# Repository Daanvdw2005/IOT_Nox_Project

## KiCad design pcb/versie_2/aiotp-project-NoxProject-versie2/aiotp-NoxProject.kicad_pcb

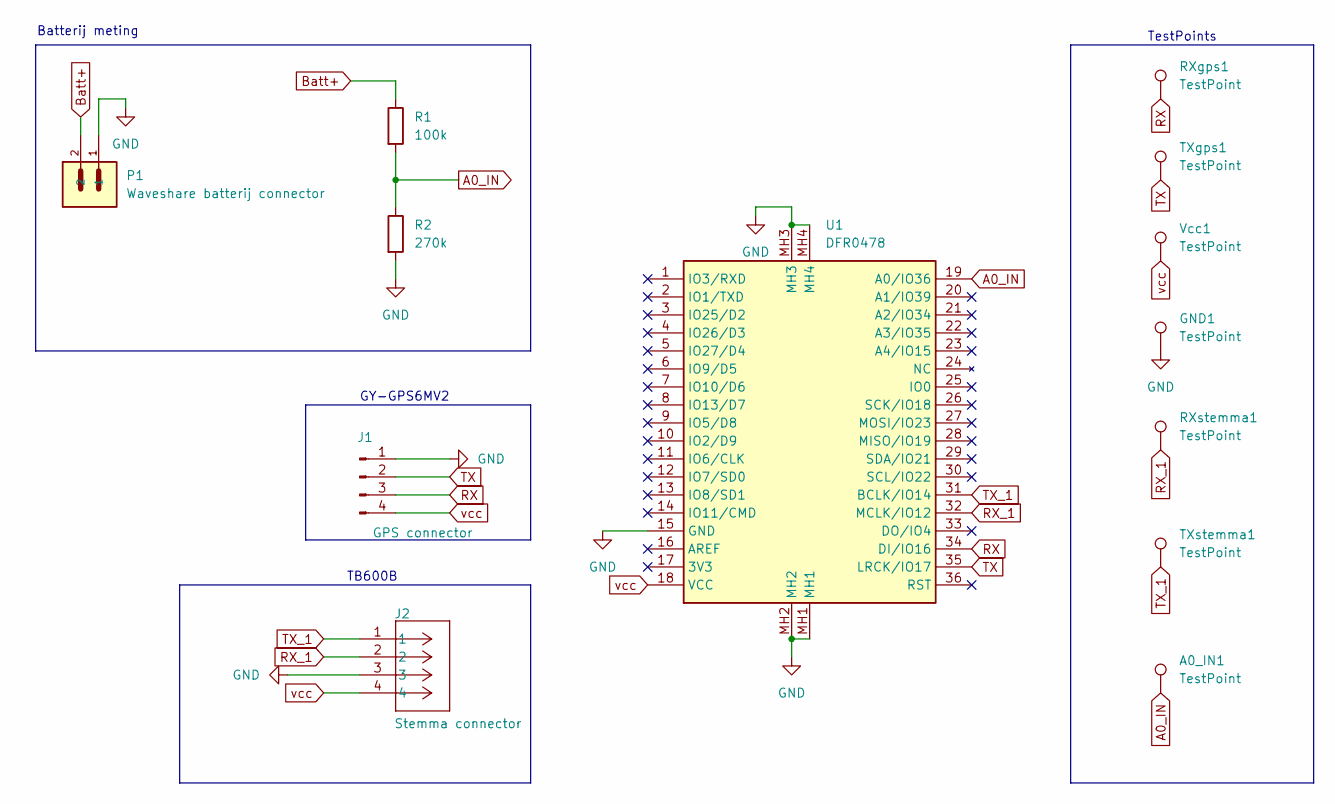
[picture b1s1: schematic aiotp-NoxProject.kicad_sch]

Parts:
A0_IN1: TestPoint; TestPoint_THTPad_D1.0mm_Drill0.5mm
GND1: TestPoint; TestPoint_THTPad_D1.0mm_Drill0.5mm
J1: GPS connector; GY-GPS6MV2
J2: Stemma connector; B4B-ZR; PARTREV N/A
P1: Waveshare batterij connector; JST_S2B-PH-SM4-TB
R1: 100k; R_0805_2012Metric
R2: 270k; R_0805_2012Metric
RXgps1: TestPoint; TestPoint_THTPad_D1.0mm_Drill0.5mm
RXstemma1: TestPoint; TestPoint_THTPad_D1.0mm_Drill0.5mm
TXgps1: TestPoint; TestPoint_THTPad_D1.0mm_Drill0.5mm
TXstemma1: TestPoint; TestPoint_THTPad_D1.0mm_Drill0.5mm
U1: DFR0478; FIREBEETLE_ESP32; Manufacturer_Part_Number DFR0478; Mouser Part Number 426-DFR0478
Vcc1: TestPoint; TestPoint_THTPad_D1.0mm_Drill0.5mm

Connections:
A0_IN: A0_IN1.1, R1.2, R2.1, U1.19 (A0/IO36)
Batt+: P1.2, R1.1
GND: GND1.1, J1.1, J2.3, P1.1, R2.2, U1.15 (GND), U1.MH1, U1.MH2, U1.MH3, U1.MH4
RX: J1.3, RXgps1.1, U1.34 (DI/IO16)
RX_1: J2.2, RXstemma1.1, U1.32 (MCLK/IO12)
TX: J1.2, TXgps1.1, U1.35 (LRCK/IO17)
TX_1: J2.1, TXstemma1.1, U1.31 (BCLK/IO14)
vcc: J1.4, J2.4, U1.18 (VCC), Vcc1.1

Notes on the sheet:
GY-GPS6MV2
TestPoints
Batterij meting
TB600B

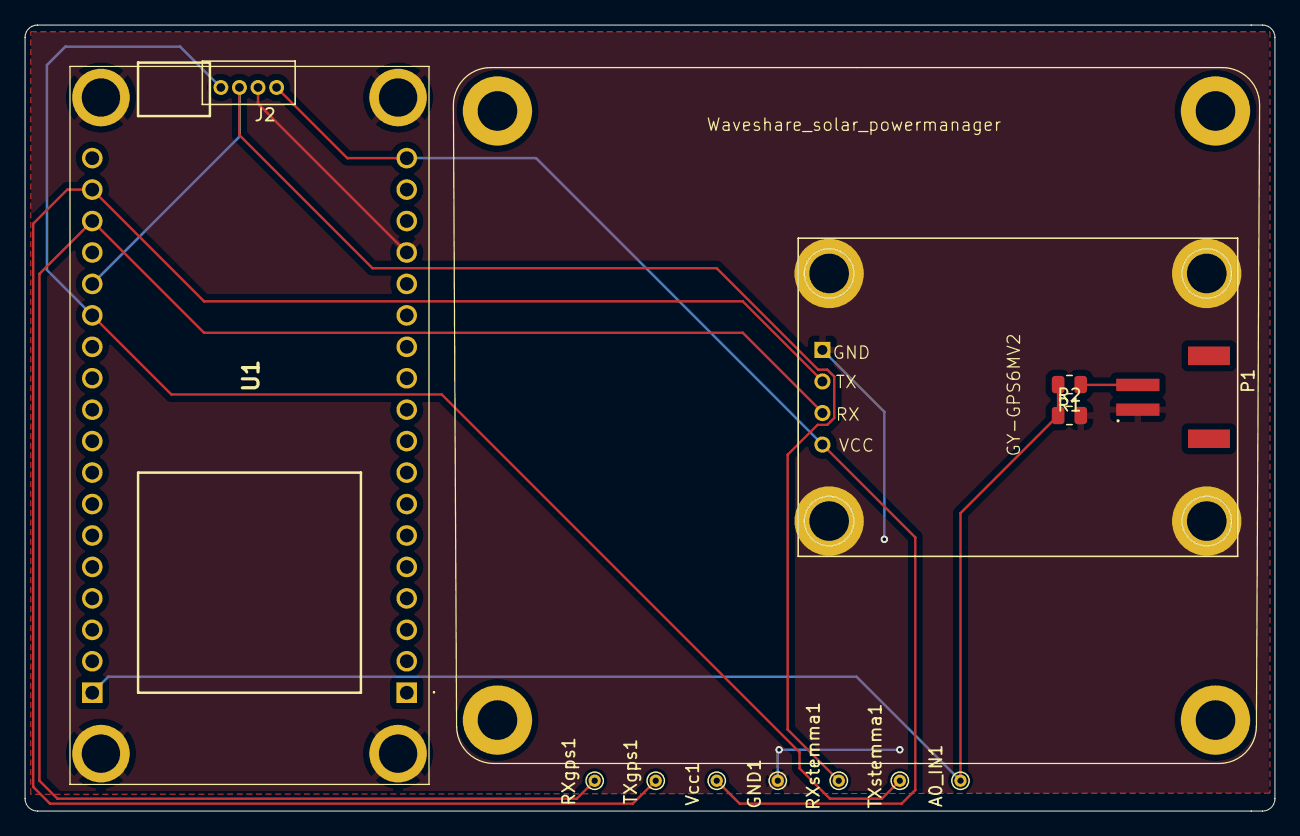
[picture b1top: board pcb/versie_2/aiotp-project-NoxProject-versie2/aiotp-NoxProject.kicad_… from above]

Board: 2 copper layers, 101.0 x 63.5 mm, 14 parts (0 on the bottom side), 8 nets.

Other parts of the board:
Waveshare_solar_powermanager: Waveshare_solar_powermanager

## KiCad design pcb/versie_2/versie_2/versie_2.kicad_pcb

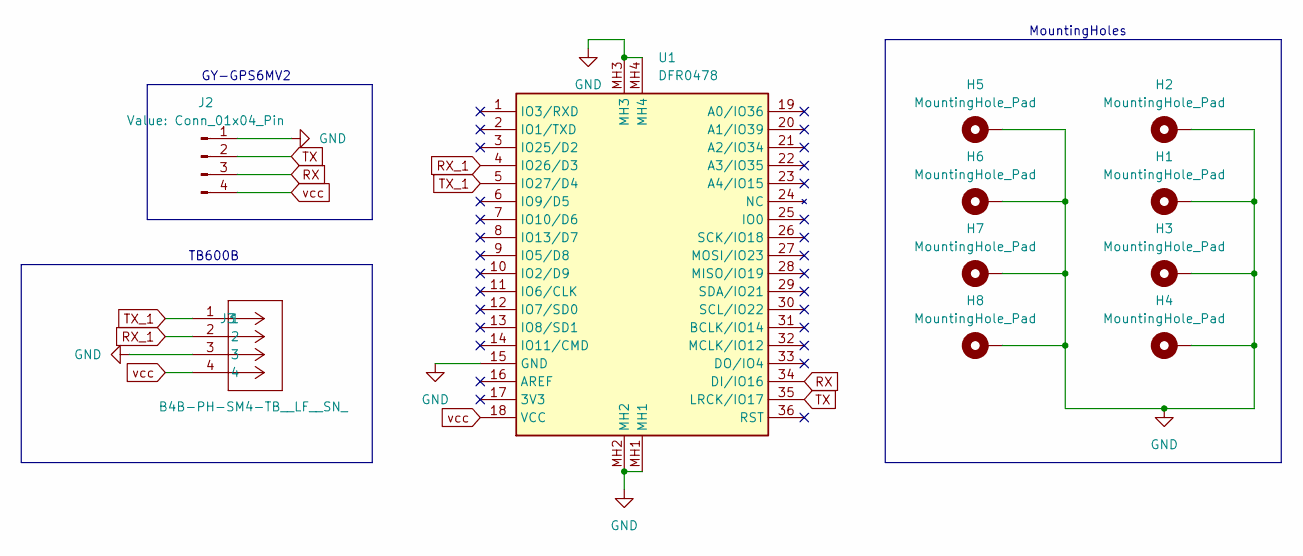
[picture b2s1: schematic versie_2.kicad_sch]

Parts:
H1, H2, H3, H4, H5, H6, H7, H8: MountingHole_Pad; MountingHole_3.2mm_M3_ISO14580_Pad_TopBottom
J2: Conn_01x04_Pin; GY-GPS6MV2
J3: B4B-PH-SM4-TB__LF__SN_; B4B-ZR; PARTREV N/A
U1: DFR0478; FIREBEETLE_ESP32; Manufacturer_Part_Number DFR0478; Mouser Part Number 426-DFR0478

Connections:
GND: H1.1, H2.1, H3.1, H4.1, H5.1, H6.1, H7.1, H8.1, J2.1, J3.3, U1.15 (GND), U1.MH1, U1.MH2, U1.MH3, U1.MH4
RX: J2.3, U1.34 (DI/IO16)
RX_1: J3.2, U1.4 (IO26/D3)
TX: J2.2, U1.35 (LRCK/IO17)
TX_1: J3.1, U1.5 (IO27/D4)
vcc: J2.4, J3.4, U1.18 (VCC)

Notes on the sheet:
GY-GPS6MV2
MountingHoles
TB600B

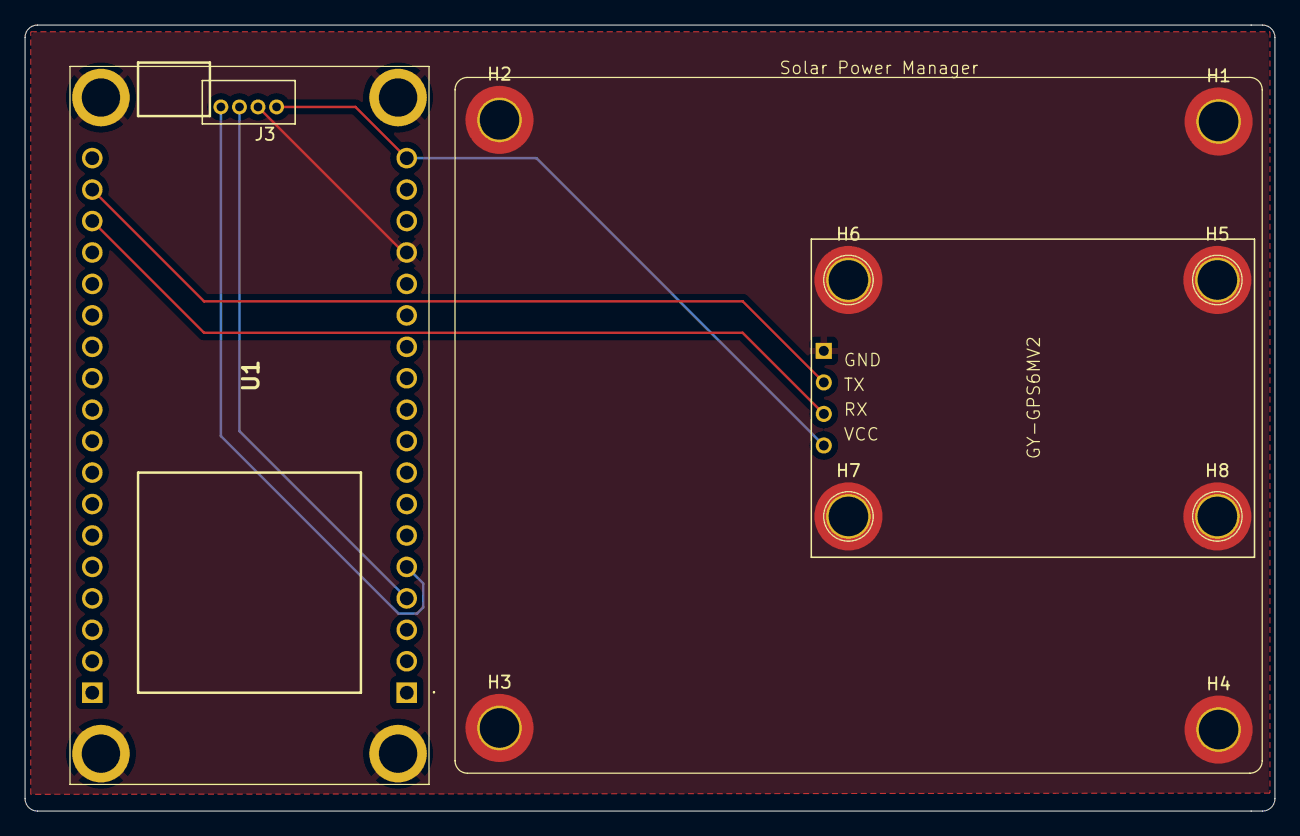
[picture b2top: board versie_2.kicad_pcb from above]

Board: 2 copper layers, 101.0 x 63.5 mm, 11 parts (0 on the bottom side), 6 nets.

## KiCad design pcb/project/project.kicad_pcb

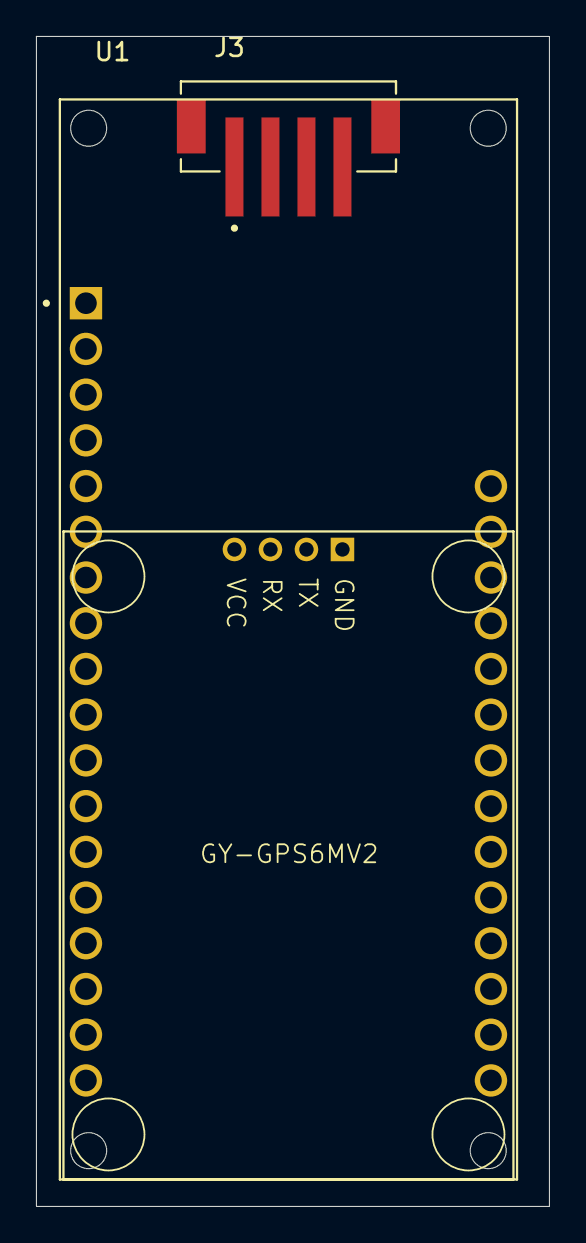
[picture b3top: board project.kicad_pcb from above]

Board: 2 copper layers, 28.5 x 65.0 mm, 3 parts (0 on the bottom side), 4 nets, no tracks yet.

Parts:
J1: 110990030; GY-GPS6MV2
J3: B4B-PH-SM4-TB__LF__SN_; JST_B4B-PH-SM4-TB__LF__SN_
U1: DFR0654; MODULE_DFR0654

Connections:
GND: J1.3, J3.3, J3.SH1 (SHIELD), J3.SH2 (SHIELD), U1.4 (GND), U1.30 (GND)
RX_1: J1.2, J3.2, U1.17 (TX)
TX_1: J1.1, J3.1, U1.18 (RX)
vcc: J1.4, J3.4, U1.32 (VCC)

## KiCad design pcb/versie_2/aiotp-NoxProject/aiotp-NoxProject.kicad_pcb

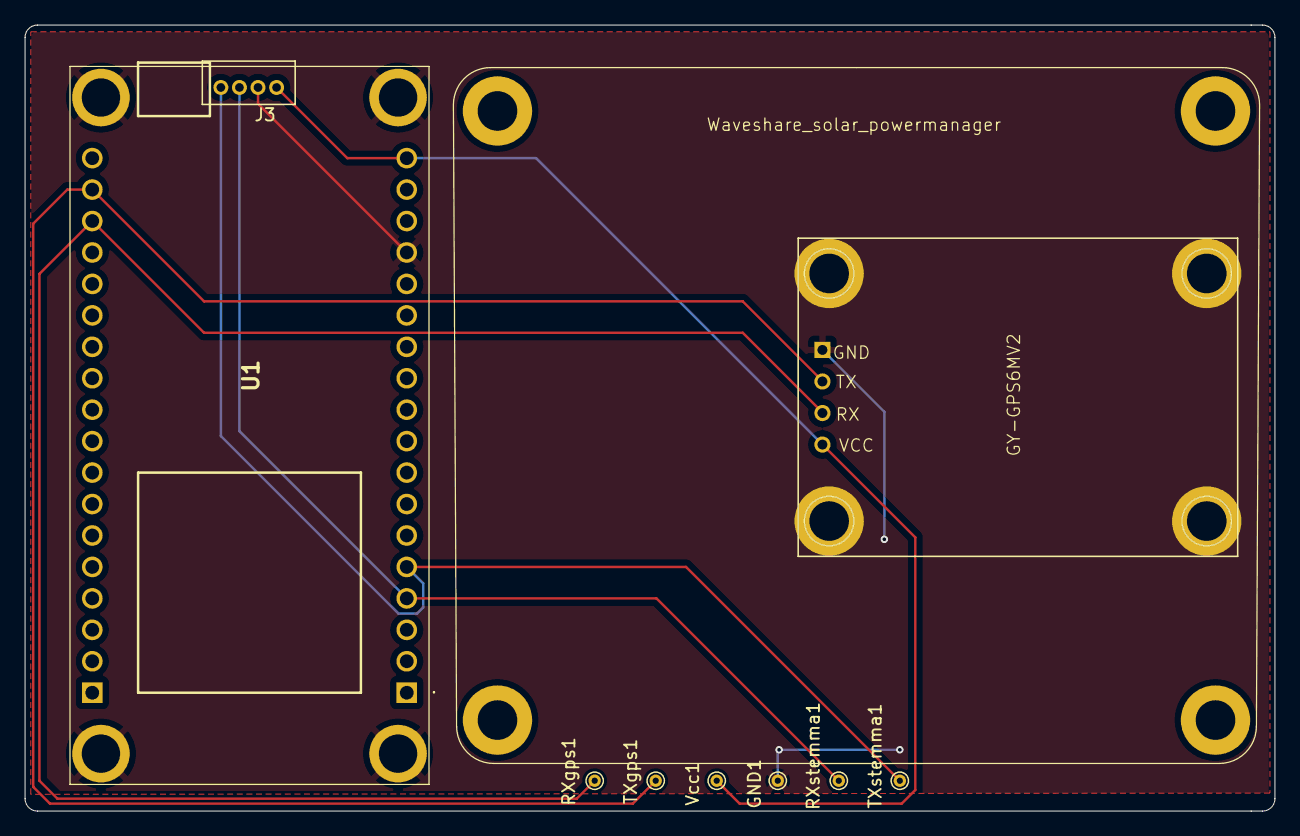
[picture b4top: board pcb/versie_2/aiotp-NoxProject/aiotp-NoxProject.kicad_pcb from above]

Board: 2 copper layers, 101.0 x 63.5 mm, 10 parts (0 on the bottom side), 6 nets.

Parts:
GND1: TestPoint; TestPoint_THTPad_D1.0mm_Drill0.5mm
J2: GPS connector; GY-GPS6MV2
J3: Stemma connector; B4B-ZR
RXgps1: TestPoint; TestPoint_THTPad_D1.0mm_Drill0.5mm
RXstemma1: TestPoint; TestPoint_THTPad_D1.0mm_Drill0.5mm
TXgps1: TestPoint; TestPoint_THTPad_D1.0mm_Drill0.5mm
TXstemma1: TestPoint; TestPoint_THTPad_D1.0mm_Drill0.5mm
U1: DFR0478; FIREBEETLE_ESP32
Vcc1: TestPoint; TestPoint_THTPad_D1.0mm_Drill0.5mm
Waveshare_solar_powermanager: Waveshare_solar_powermanager

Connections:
GND: GND1.1, J2.1, J3.3, U1.15 (GND), U1.MH1, U1.MH2, U1.MH3, U1.MH4
RX: J2.3, RXgps1.1, U1.34 (DI/IO16)
RX_1: J3.2, RXstemma1.1, U1.4 (IO26/D3)
TX: J2.2, TXgps1.1, U1.35 (LRCK/IO17)
TX_1: J3.1, TXstemma1.1, U1.5 (IO27/D4)
vcc: J2.4, J3.4, U1.18 (VCC), Vcc1.1

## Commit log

2025-09-19 test_git
    test_git
2025-09-19 Blokdiagram_flow_V1
    Blokdiagram_flow_V1
2025-09-19 Create documentatie.md
    start documentatie
2025-09-19 navigatie ingesteld
    navigatie ingesteld
2025-09-20 Update documentatie.md
    Update documentatie Daan
2025-10-03 Toevoeging_blokdiagram_doelstelling
2025-10-03 Hello_world_werkend
    https://www.youtube.com/watch?v=sjNIbdBBm98
2025-10-03 15:45
2025-10-03 esp32Xgps_nognietwerkend
2025-10-07 Update Documentatie
2025-10-10 update documentatie
    toevoeging fire beetle
2025-10-10 hernoeming
2025-10-10 Update main.c
    werkende test-codes:
    GPS-module
    TB600B
    combinatie code
2025-10-10 pcb design
2025-10-10 update presentatie
2025-10-11 hardware lijst+ documantatie
    het aanmaken van de harware lijst en nog enkele updates aan de documantatie
2025-10-12 Update planning
2025-10-14 Update_structuur
2025-10-14 Delete Documentatie/.$Blakdiagram_doelstelling.drawio.bkp
    niet meer nodig, juiste versie geupload
2025-10-14 afbeeldingen_resize
2025-10-14 Image_update
2025-10-14 Update_documentatie_images
2025-10-17 Update_code
    nog niet werkend gekregen met nieuwe versie
2025-10-17 PCB_2eversie
2025-10-18 PCB_update
2025-10-18 PCB_update_finaal
2025-10-23 update_bestellingen
2025-10-23 test_lorawan
    mislukt
2025-10-24 verwijderen mislukte lorawan
2025-11-07 testen c
    kan nog steeds niet uploaden
2025-11-07 pinout gps
    aanpassing pcb zodat de pinnen de juiste afstand hebben om de gps aan te sluiten
2025-11-07 pcb mod
    aanpassing aan de pcb zodat de gps kan geplaatst worden.
2025-11-07 aanpassing
    voorstel
2025-11-07 pcb
    omdraaien tb600
2025-11-13 toevoeging lora
    mogelijks werkende test lora
2025-11-14 lora
2025-11-14 pcb
    aanpassingen met gerber files
2025-11-14 lora
    aanpassingen zodat ik de lora kan in gebruik nemen
2025-11-14 lora
    eerst werkende test met de ttn en lora
2025-11-14 lora
    meerdere waardes doorsturen:
    -temperatuur
    -humi
    -licht
    met test waardes
2025-11-14 pogingen ttn
2025-11-14 lora
    lora + tb600b
    -volledige integratie van de gassensor met ttn
2025-11-14 update_3d_design_and_routing_pcb_versie2
2025-11-21 PCB update versie 2
2025-11-21 drone opzet
2025-11-21 werkende ttn
2025-11-28 update PCB en Drone
2025-11-28 Database_credentials
2025-11-28 gps debug
    enkele aanpassingen in de hoop dat de gps zou werken
2025-11-28 aanpassingen ttn
    toevoeging van gps time en het correct sturen van de gps
2025-11-28 gps epoch
    zorgen dat de gps enkel epochs zal gaan gebruiken
2025-11-28 database integratie
2025-12-05 aanpassing code
2025-12-05 afstellen gps
    Er zat nog een fout in onze omzetting van de altitude en longitude. Deze zijn nu bijgesteld.
2025-12-12 PCB en influx en node
2025-12-19 toevoegen low power
    low power modes integreren
